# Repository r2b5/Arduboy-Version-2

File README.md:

# Arduboy Version 2

Arduboy Version 2 is a custom-built handheld game console based on the original **DIY Mini Retro Game Console** by **MaDDy Regal** (Uttar Pradesh, India), published on Instructables.

Unlike the original design, this version integrates the Arduino Nano's **ATmega32U4** microcontroller directly onto a custom PCB. It also features a USB Type-C connector for power and programming, an integrated Li-ion battery charging circuit, and a larger OLED display.

## Hardware

- **Microcontroller:** ATmega32U4-AU
- **Display:** 2.42" 128×64 SPI OLED (Joy-it COM-OLED2.42, SSD1309 controller)
- Integrated Li-ion battery charging circuit MCP73831
- Custom-designed PCB

## Software

- Arduino IDE
- CadSoft Eagle

> **Note:**  
> The game source code is **not my own work**. It consists of example projects that have been adapted to run on this hardware implementation.
>
> 

## Flashing the Bootloader

An **Arduino Uno** can be used as an ISP programmer to burn the bootloader.

The board provides the standard **6-pin Arduino ISP header**. Before burning the bootloader, select **Arduino Leonardo** as the target board in the Arduino IDE.

| Arduino Uno | Arduboy (Leonardo) |
|--------------|--------------------|
| D12 | MISO |
| 5V | 5V |
| D13 | SCK |
| D11 | MOSI |
| D10 | RESET |
| GND | GND |

After wiring the programmer, use **Tools → Burn Bootloader** in the Arduino IDE.

## Required Changes to `Arduboy2Core.cpp`

Since this hardware differs from the original Arduboy, a small modification to `Arduboy2Core.cpp` is required for the SSD1309 display to render correctly.

Replace the column and page address initialization with:

```cpp
// Set column address range
0x21, 0x00, COLUMN_ADDRESS_END,

// Set page address range
0x22, 0x00, PAGE_ADDRESS_END
```

## Project Goals

The primary objective of this project is to teach apprentices and interns the fundamentals of microcontroller programming while providing a practical understanding of how embedded electronic systems work.

In addition, the project serves as a foundation for developing more advanced retro gaming consoles and other embedded systems.

## Credits

- Original DIY Mini Retro Game Console concept by **MaDDy Regal**
- Original game source code by **different authors**
- Hardware redesign and PCB development by **Jesus Suarez**

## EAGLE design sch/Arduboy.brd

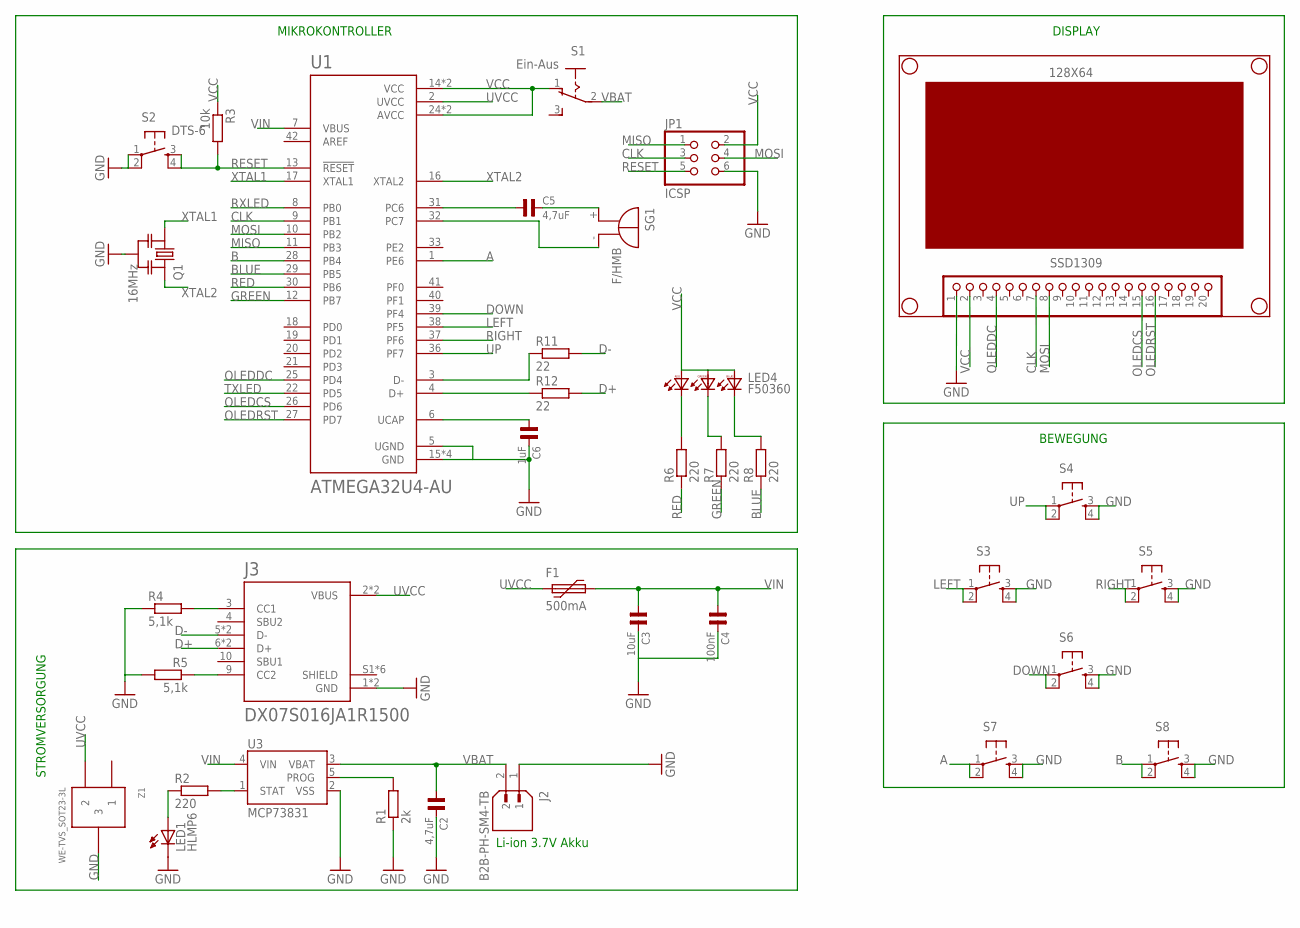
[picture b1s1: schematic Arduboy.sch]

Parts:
128X64: SSD1309; 1X20
C2, C5: 4,7uF; 0204
C3: 10uF; 0204
C4: 100nF; 0204
C6: 1uF; 0204
F1: 500mA; MF-5,1
J2: B2B-PH-SM4-TB; JST_B2B-PH-SM4-TB
J3: DX07S016JA1R1500; JAE_DX07S016JA1R1500
JP1: ICSP; 2X03
LED1: HLMP6
LED4: F50360
Q1: 16MHz; RESONATOR_MURATA3
R1: 2k; M0805
R2, R6, R7, R8: 220; M0805
R3: 10k; M0805
R4, R5: 5,1k; M0805
R11, R12: 22; M0805
S1: Ein-Aus; 255SB
S2: DTS-6
S3, S4, S5, S6, S7, S8: TAC_SWITCHPTH; TACTILE-PTH
SG1: F/HMB
U1: ATMEGA32U4-AU; QFP80P1200X1200X120-44N
U3: MCP73831; SOT23-5
Z1: WE-TVS_SOT23-3L

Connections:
A: S7.1, S7.2, U1.1 (PE6)
B: S8.1, S8.2, U1.28 (PB4)
BLUE: R8.1, U1.29 (PB5)
CLK: 128X64.7, JP1.3, U1.9 (PB1)
D+: J3.6 (D+), J3.7 (D+), R12.2
D-: J3.5 (D-), J3.8 (D-), R11.2
DOWN: S6.1, S6.2, U1.39 (PF4)
GND: 128X64.1, C2.2, C3.2, C4.2, C6.2, J2.1, J3.1 (GND), J3.12 (GND), JP1.6, LED1.K, Q1.2, R1.1, R4.1, R5.2, S2.1, S2.2, S3.3, S3.4, S4.3, S4.4, S5.3, S5.4, S6.3, S6.4, S7.3, S7.4, S8.3, S8.4, U1.5 (UGND), U1.15 (GND), U1.23 (GND), U1.35 (GND), U1.43 (GND), U3.2 (VSS), Z1.3
GREEN: R7.1, U1.12 (PB7)
LEFT: S3.1, S3.2, U1.38 (PF5)
MISO: JP1.1, U1.11 (PB3)
MOSI: 128X64.8, JP1.4, U1.10 (PB2)
unnamed: R12.1, U1.4 (D+)
unnamed: R11.1, U1.3 (D-)
unnamed: R1.2, U3.5 (PROG)
unnamed: R2.2, U3.1 (STAT)
unnamed: LED1.A, R2.1
unnamed: C5.1, U1.31 (PC6)
unnamed: SG1.-, U1.32 (PC7)
unnamed: C5.2, SG1.+
unnamed: J3.9 (CC2), R5.1
unnamed: LED4.RC, R6.2
unnamed: LED4.GC, R7.2
unnamed: LED4.BC, R8.2
unnamed: C6.1, U1.6 (UCAP)
unnamed: J3.3 (CC1), R4.2
OLEDCS: 128X64.15, U1.26 (PD6)
OLEDDC: 128X64.4, U1.25 (PD4)
OLEDRST: 128X64.16, U1.27 (PD7)
RED: R6.1, U1.30 (PB6)
RESET: JP1.5, R3.2, S2.3, S2.4, U1.13 (!RESET)
RIGHT: S5.1, S5.2, U1.37 (PF6)
RXLED: U1.8 (PB0)
TXLED: U1.22 (PD5)
UP: S4.1, S4.2, U1.36 (PF7)
UVCC: F1.1, J3.2 (VBUS), J3.11 (VBUS), U1.2 (UVCC), Z1.2
VBAT: C2.1, J2.2, S1.2, U3.3 (VBAT)
VCC: 128X64.2, JP1.2, LED4.BA, LED4.GA, LED4.RA, R3.1, S1.1 (O), U1.14 (VCC), U1.24 (AVCC), U1.34 (VCC), U1.44 (AVCC)
VIN: C3.1, C4.1, F1.2, U1.7 (VBUS), U3.4 (VIN)
XTAL1: Q1.1, U1.17 (XTAL1)
XTAL2: Q1.3, U1.16 (XTAL2)

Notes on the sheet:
BEWEGUNG
STROMVERSORGUNG
MIKROKONTROLLER
DISPLAY
Li-ion 3.7V Akku

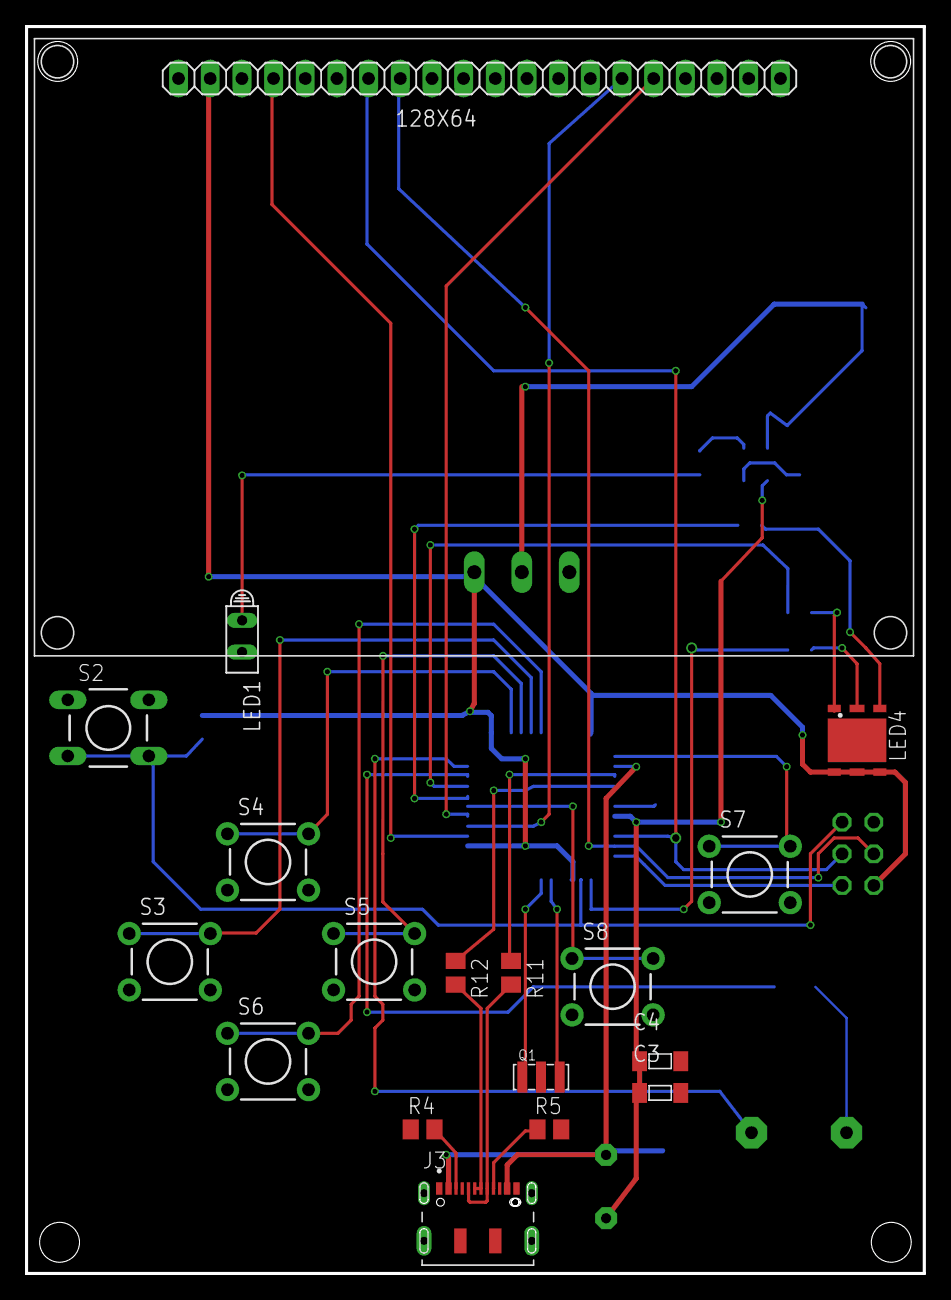
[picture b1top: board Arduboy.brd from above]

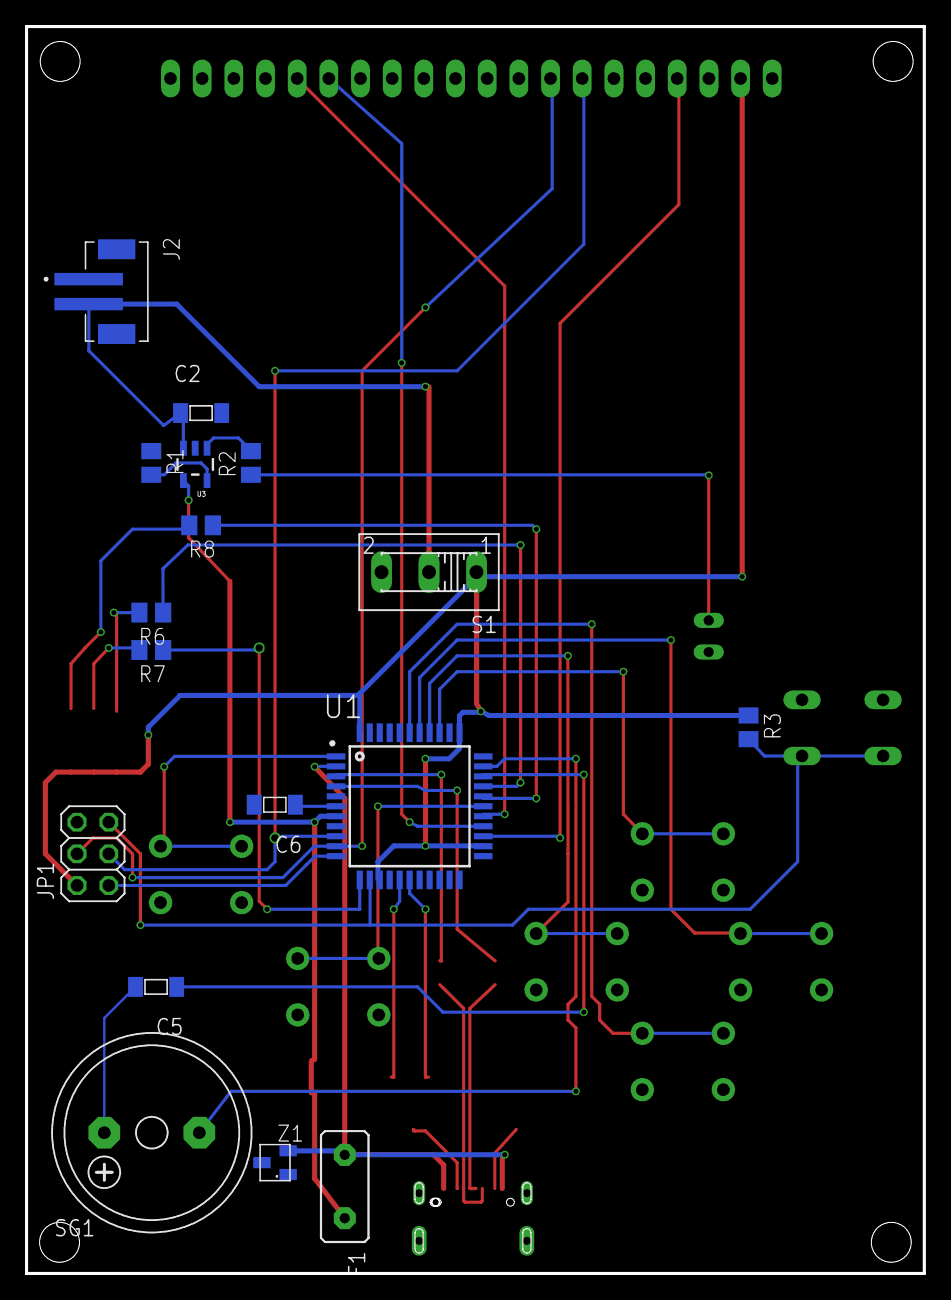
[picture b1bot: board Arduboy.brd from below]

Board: 2 copper layers, 72.0 x 100.0 mm, 35 parts (17 on the bottom side), 39 nets.

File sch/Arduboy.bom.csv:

"Qty";"Value";"Device";"Package";"Parts";"Description";"AVAILABILITY";"CHECK_PRICES";"DESCRIPTION";"HEIGHT";"MF";"MP";"MPN";"OC_FARNELL";"OC_NEWARK";"PACKAGE";"PRICE";"PURCHASE-URL";"SNAPEDA_LINK";
"6";"";"TAC_SWITCHPTH";"TACTILE-PTH";"S3, S4, S5, S6, S7, S8";"Momentary Switch";"";"";"";"5";"";"";"";"";"";"";"";"";"";
"1";"100nF";"C0204";"0204";"C4";"smallest SMD capacitor";"";"";"";"";"";"";"";"";"";"";"";"";"";
"1";"10k";"R-EU_M0805";"M0805";"R3";"RESISTOR, European symbol";"";"";"";"";"";"";"";"";"";"";"";"";"";
"1";"10uF";"C0204";"0204";"C3";"smallest SMD capacitor";"";"";"";"";"";"";"";"";"";"";"";"";"";
"1";"16MHz";"RESONATOR-MURATACSTCR_G";"RESONATOR_MURATA3";"Q1";"Murata ceramic Resonator "ceralock" CSTCE series";"";"";"";"";"";"";"";"";"";"";"";"";"";
"1";"1uF";"C0204";"0204";"C6";"smallest SMD capacitor";"";"";"";"";"";"";"";"";"";"";"";"";"";
"2";"22";"R-EU_M0805";"M0805";"R11, R12";"RESISTOR, European symbol";"";"";"";"";"";"";"";"";"";"";"";"";"";
"4";"220";"R-EU_M0805";"M0805";"R2, R6, R7, R8";"RESISTOR, European symbol";"";"";"";"";"";"";"";"";"";"";"";"";"";
"1";"2k";"R-EU_M0805";"M0805";"R1";"RESISTOR, European symbol";"";"";"";"";"";"";"";"";"";"";"";"";"";
"2";"4,7uF";"C0204";"0204";"C2, C5";"smallest SMD capacitor";"";"";"";"";"";"";"";"";"";"";"";"";"";
"2";"5,1k";"R-EU_M0805";"M0805";"R4, R5";"RESISTOR, European symbol";"";"";"";"";"";"";"";"";"";"";"";"";"";
"1";"500mA";"MF-R055-5,1";"MF-5,1";"F1";"MultiFuse Polyfuse Overcurrent Protectors";"";"";"";"";"";"";"";"";"";"";"";"";"";
"1";"ATMEGA32U4-AU";"ATMEGA32U4-AU";"QFP80P1200X1200X120-44N";"U1";"Check availability";"In Stock";"https://www.snapeda.com/parts/ATMEGA32U4-AU/Microchip+Techno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";"                                                      Microcontroller, USB controller 16/32K of ISP flash, TQFP44 industrial, 8-bit | Microchip Technology Inc. ATMEGA32U4-AU                                              ";"";"Microchip Technology";"ATMEGA32U4-AU";"";"";"";"TQFP-44 Microchip";"None";"https://www.snapeda.com/api/url_track_click_mouser/?unipart_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 Technology&part_name=ATMEGA32U4-AU&search_term=atmega32u4";"https://www.snapeda.com/parts/ATMEGA32U4-AU/Microchip+Techno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";
"1";"B2B-PH-SM4-TB";"B2B-PH-SM4-TB";"JST_B2B-PH-SM4-TB";"J2";"Check availability";"In Stock";"https://www.snapeda.com/parts/B2B-PH-SM4-TB/JST/view-part/?ref=eda";"                                                      Connector Header Surface Mount 2 position 0.079 (2.00mm)                                              ";"5";"JST";"B2B-PH-SM4-TB";"";"";"";"NON STANDARD-2 JST";"None";"https://www.snapeda.com/api/url_track_click_mouser/?unipart_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 ph 2mm";"https://www.snapeda.com/parts/B2B-PH-SM4-TB/JST/view-part/?ref=snap";
"1";"DTS-6";"DTS-6";"DTS-6";"S2";"";"";"";"";"7";"";"";"";"";"";"";"";"";"";
"1";"DX07S016JA1R1500";"DX07S016JA1R1500";"JAE_DX07S016JA1R1500";"J3";"Check availability";"In Stock";"https://www.snapeda.com/parts/DX07S016JA1R1500/JAE+Electroni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";"                                                      USB-C (USB TYPE-C) USB 2.0 Receptacle Connector 24 (16+8 Dummy) Position Surface Mount, Right Angle";" Through Hole                                              ";"4";"JAE Electronics";"DX07S016JA1R1500";"";"";"";"None";"None";"https://www.snapeda.com/api/url_track_click_mouser/?unipart_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 Electronics&part_name=DX07S016JA1R1500&search_term=jae, gewinkelt dx usb-steckverbinder buchse usb typ c 1, oberfläche usb 2.0";
"1";"Ein-Aus";"255SB";"255SB";"S1";"SLIDING SWITCH";"";"";"";"";"";"";"";"";"";"";"";"";"";
"1";"F/HMB";"F/HMB";"F/HMB";"SG1";"BUZZER Source: Buerklin";"";"";"";"8";"";"";"";"unknown";"unknown";"";"";"";"";
"1";"F50360";"F50360";"F50360";"LED4";"Full color Z-Power LED RGB P5-II Series";"";"";"";"";"";"";"";"";"";"";"";"";"";
"1";"HLMP6";"HLMP6";"HLMP6";"LED1";"LED";"";"";"";"4";"AGILENT TECHNOLOGIES";"";"HLMP-6500";"1652490";"40K0088";"";"";"";"";
"1";"ICSP";"PINHD-2X3";"2X03";"JP1";"PIN HEADER";"";"";"";"5";"";"";"";"";"";"";"";"";"";
"1";"MCP73831";"MCP73831";"SOT23-5";"U3";"Miniature single cell, fully integrated Li-Ion, Li-polymer charge management controller";"";"";"";"";"";"";"";"";"";"";"";"";"";
"1";"SSD1309";"PINHD-1X20";"1X20";"128X64";"PIN HEADER";"";"";"";"8";"";"";"";"";"";"";"";"";"";
"1";"WE-TVS_SOT23-3L";"WE-TVS_SOT23-3L";"WE-TVS_SOT23-3L";"Z1";"TVS Diode Array WE-TVS";"";"";"";"";"";"";"";"";"";"";"";"";"";

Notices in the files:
parts and their libraries:
m-pad-2.1: License : GNU General Public License version 2 (see bottom)
SparkFun-Electromechanical: Licensing: CC v3.0 Share-Alike You are welcome to use this library for commercial purposes.
wuerth_elektronik_eisos__v6.0: Copyright: Würth Elektronik eiSos
